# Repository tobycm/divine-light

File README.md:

# Divine Light

CH572-powered RGB flashlight with BLE for remote control from phone. Uses SK6812s for high brightness and 2 LiPos for portable usage. Provides charging port and one reverse charging port (acts as power bank).

## PCB

## BOM

| Description | Quantity | Part # | Unit price | Extended Price USD | Product Link |
| :--- | :---: | :--- | :---: | :---: | :--- |
| Lithium Battery SOT-23-6 Battery Management | 5 | HY2120-CB | 0.251 | 1.26 | https://www.lcsc.com/product-detail/C116509.html |
| Battery Charging IC Battery Balancing IC Lithium-ion/Polymer VQFN-24-EP(4x4) | 2 | IP2326 | 0.6377 | 1.28 | https://www.lcsc.com/product-detail/C2832094.html |
| N-Channel Array 20V 6A 1.5W Surface Mount SOT-23-6L | 10 | FS8205A | 0.058 | 0.58 | https://www.lcsc.com/product-detail/C908265.html |
| 125mW 330Ω 150V Thick Film Resistor ±100ppm/°C ±1% 0805 Chip Resistor - Surface Mount RoHS | 100 | RC0805FR-07330RL | 0.0061 | 0.61 | https://www.lcsc.com/product-detail/C105878.html |
| 22uF ±20% 25V Ceramic Capacitor X5R 0805 | 30 | CL21A226MAYNNNE | 0.1078 | 3.23 | https://www.lcsc.com/product-detail/C602037.html |
| 10uF ±20% 10V Ceramic Capacitor X5R 0603 | 20 | CL10A106MP8NNNC | 0.0173 | 0.35 | https://www.lcsc.com/product-detail/C85713.html |
| Step-down type 600kHz Adjustable 2.5A SOT-23-6 Voltage Regulators - DC DC Switching Regulators | 5 | TP6327GS6-A | 0.3619 | 1.81 | https://www.lcsc.com/product-detail/C2901328.html |
| SMD-4P, 5.4x5mm LED Addressable, Specialty RoHS | 50 | SK6812 | 0.0726 | 3.63 | https://www.lcsc.com/product-detail/C5378720.html |
| 125mW 2kΩ 150V Thin Film Resistor ±50ppm/°C ±0.1% 0805 Chip Resistor - Surface Mount RoHS | 10 | RT0805BRE072KL | 0.0443 | 0.44 | https://www.lcsc.com/product-detail/C706274.html |
| 9.5A 2.2uH ±20% 15mΩ 10A Molded inductor SMD, 7x6.6mm Fixed Inductors RoHS | 10 | APH0630T2R2M | 0.0817 | 0.82 | https://www.lcsc.com/product-detail/C5349701.html |
| RES 180kΩ ±1% 250mW 1206 | 50 | 1206W4F1803T5E | 0.0145 | 0.725 | https://www.lcsc.com/product-detail/C17923.html |
| 5.1kΩ ±1% 100mW 0603 Thick Film Resistor | 100 | FRC0603F5101TS | 0.0015 | 0.15 | https://www.lcsc.com/product-detail/C2907044.html |
| USB-C (USB TYPE-C) Receptacle Connector 16 Position Surface Mount, Right Angle | 20 | TYPE-C 16PIN 2MD(073) | 0.0718 | 1.44 | https://www.lcsc.com/product-detail/C2765186.html |
| 100nF ±10% 50V Ceramic Capacitor X7R 0603 | 100 | CL10B104KB8NNNC | 0.0072 | 0.72 | https://www.lcsc.com/product-detail/C1591.html |
| 56kΩ ±1% 100mW 0603 Thick Film Resistor | 100 | FRC0603F5602TS | 0.0018 | 0.18 | https://www.lcsc.com/product-detail/C2907053.html |
| 100mW 10kΩ 75V Thick Film Resistor ±100ppm/°C ±1% 0603 Chip Resistor - Surface Mount RoHS | 100 | RC0603FR-0710KL | 0.0027 | 0.27 | https://www.lcsc.com/product-detail/C98220.html |
| NTC Thermistor 100kΩ Surface Mount 0603 | 50 | CMFA104J3950HANT | 0.0165 | 0.83 | https://www.lcsc.com/product-detail/C338607.html |
| 82kΩ ±1% 100mW 0603 Thick Film Resistor | 100 | FRC0603F8202TS | 0.0016 | 0.16 | https://www.lcsc.com/product-detail/C2907072.html |
| Purple LED Indication - Discrete 0603 | 50 | XL-1608UVC-04 | 0.0122 | 0.61 | https://www.lcsc.com/product-detail/C7371898.html |
| RISC-V 32 Bit 100MHz QFN-20-EP(3x3) Microcontrollers | 10 | CH572D | 0.312 | 3.12 | https://www.lcsc.com/product-detail/C46597863.html |
| 8pF 50V Ceramic Capacitor NP0 0603 | 100 | CC0603CRNPO9BN8R0 | 0.0066 | 0.66 | https://www.lcsc.com/product-detail/C327316.html |
| Slide Switch SPDT 2A @ 125V Through Hole, Right Angle Rectangular Columnar 12.7mm | 5 | SS12D10G6-WJ | 0.2314 | 1.16 | https://www.lcsc.com/product-detail/C7431059.html |
| 100mW 0Ω 75V Thick Film Resistor ±400ppm/°C ±1% 0603 Chip Resistor - Surface Mount | 100 | FRC0603F0000TS | 0.0015 | 0.15 | https://www.lcsc.com/product-detail/C2906974.html |
| Connector Header 2 position 2mm Pitch 2A Right Angle -25°C~+85°C | 20 | S2B-PH-K-S(LF)(SN) | 0.04 | 0.80 | https://www.lcsc.com/product-detail/C173752.html |
| 74mΩ 2 SOT-583 OR Controllers, Ideal Diodes RoHS | 1 | LM66200DRLR | 0.4213 | 0.4213 | https://www.lcsc.com/product-detail/C3235556.html |
| 4.7uF ±10% 10V Ceramic Capacitor X5R 0603 | 50 | CL10A475KP8NNNC | 0.0128 | 0.64 | https://www.lcsc.com/product-detail/C1705.html |
| 4 480Mbps USB 2.0 QFN-16(3x3) Interface Controllers RoHS | 1 | CH334P | 0.4073 | 0.4073 | https://www.lcsc.com/product-detail/C5373042.html |
| 300kΩ ±1% 250mW 1206 Thick Film Resistor | 100 | FRC1206F3003TS | 0.004 | 0.40 | https://www.lcsc.com/product-detail/C2933671.html |
| LCSC Shipping | 1 | LCSC Shipping | 12.38 | 12.38 | https://www.lcsc.com/ |
| PCB | 1 | PCB | 2 | 2.00 | https://jlcpcb.com/ |
| Stencil | 1 | Stencil | 3.1 | 3.10 | https://jlcpcb.com/ |
| JLCPCB Shipping | 1 | JLCPCB Shipping | 10.12 | 10.12 | https://jlcpcb.com/ |
| 103040 LiPo batteries | 2 | 103040 | 3.97 | 7.94 | https://ydlbattery.com/en-ca/products/3-7v-1200mah-103040-lithium-polymer-ion-battery?variant=42093666959513 |
| YDL Shipping | 1 | YDL Shipping | 6.98 | 6.98 | https://ydlbattery.com/en-ca |
| | | **Total:** | | **69.37** | |

## End notes

Made with <3 by @tobycm

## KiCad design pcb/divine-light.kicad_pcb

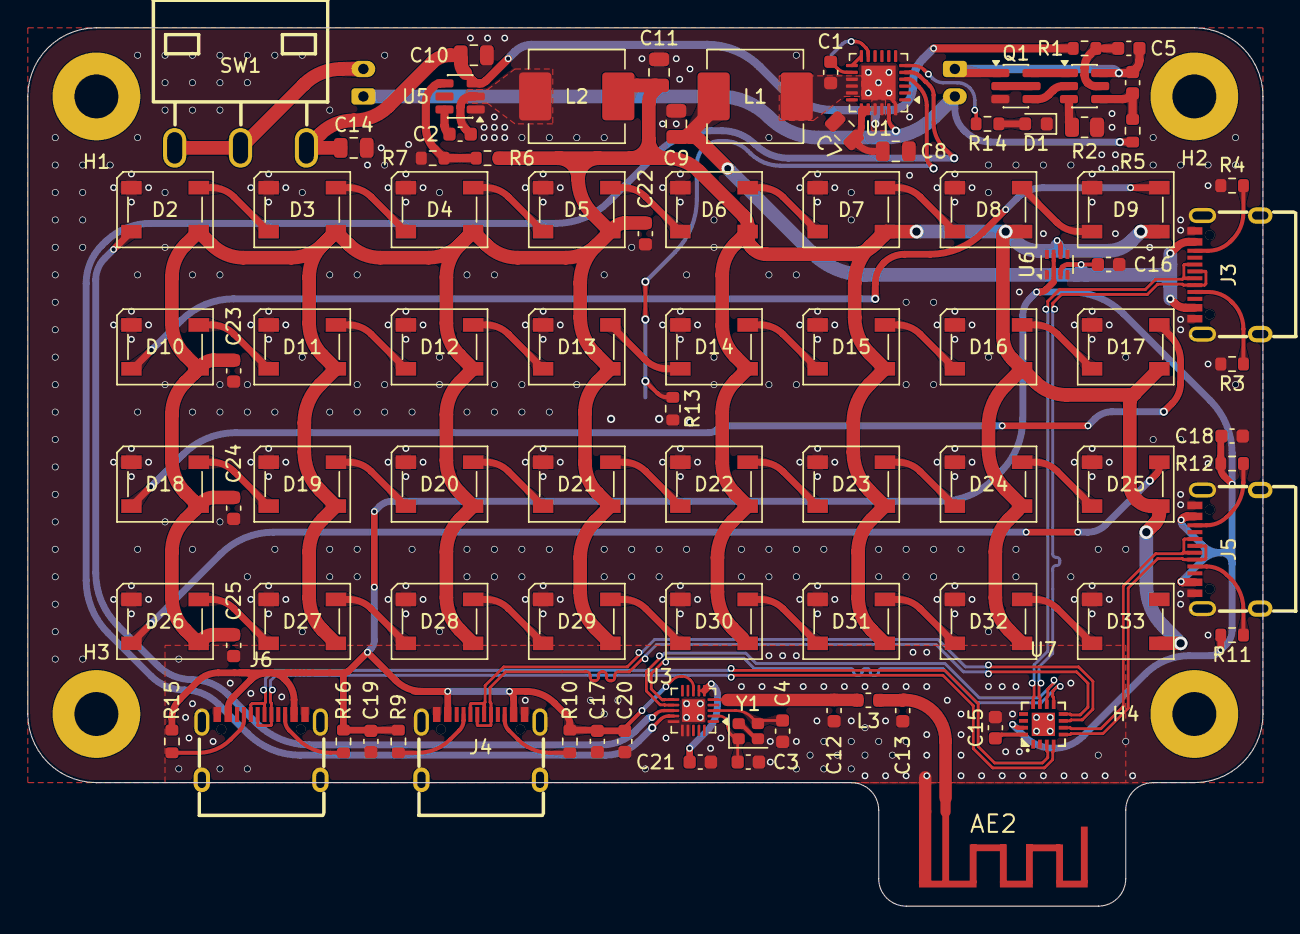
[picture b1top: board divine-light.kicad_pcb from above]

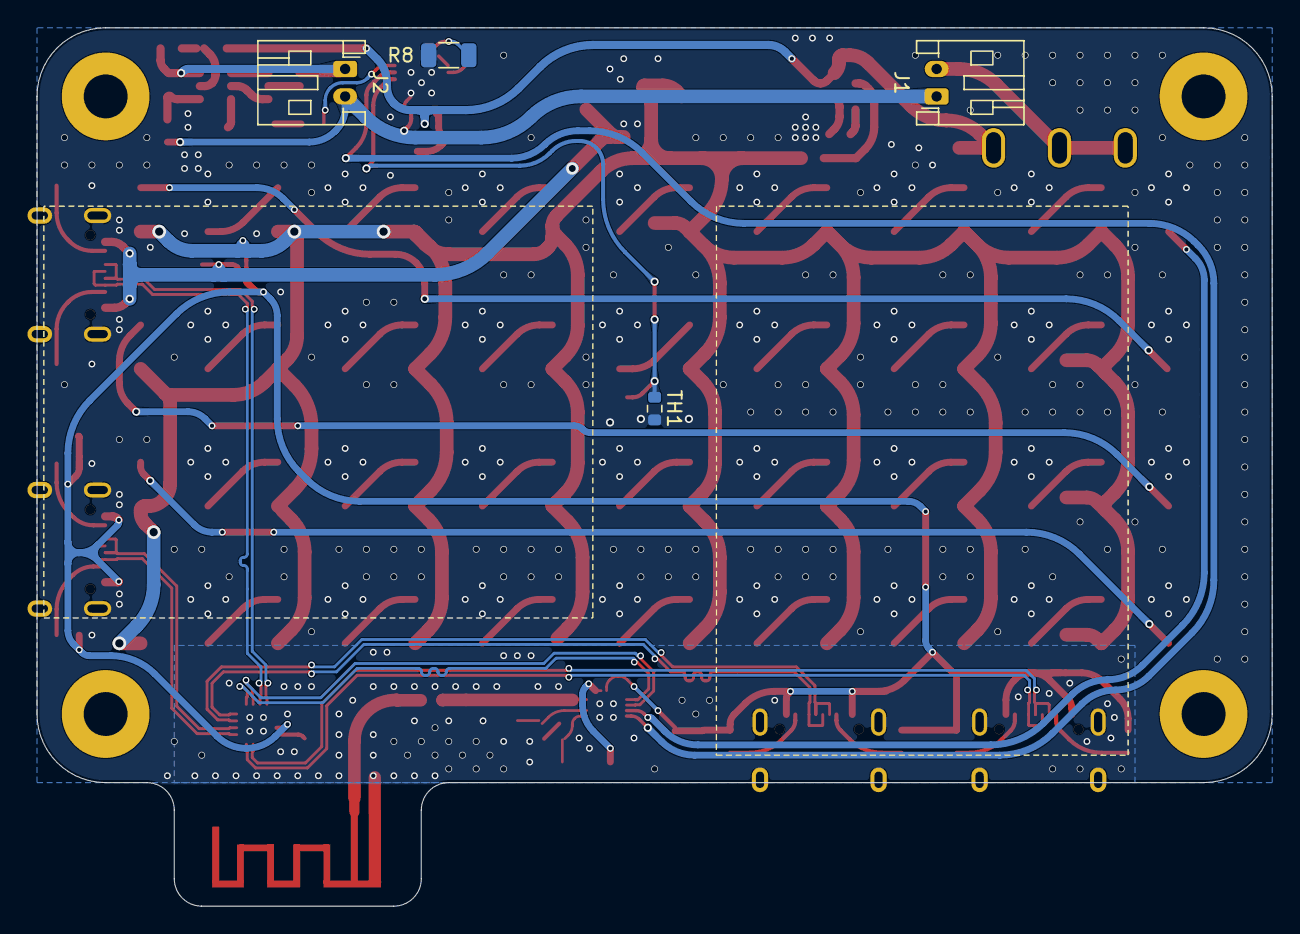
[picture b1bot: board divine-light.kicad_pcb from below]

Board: 2 copper layers, 90.0 x 64.0 mm, 98 parts (4 on the bottom side), 82 nets.

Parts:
AE2: Antenna_Shield; ANT-F-1-2.4G-1.6MM-FR4-WCH
C1, C2, C5, C6: 100n; C_0603_1608Metric
C3, C4: 8p; C_0603_1608Metric
C7, C8, C9, C10, C11, C14: 22u; C_0805_2012Metric
C12, C13: C; C_0603_1608Metric
C15, C16, C17, C18, C19, C20, C21, C22, C23, C24, C25: 4.7u; C_0603_1608Metric
D1: LED; LED_0603_1608Metric
D2, D3, D4, D5, D6, D7, D8, D9, D10, D11, D12, D13, D14, D15, D16, D17, D18, D19, D20, D21, D22, D23, D24, D25, D26, D27, D28, D29, D30, D31, D32, D33: SK6812; LED_SK6812_PLCC4_5.0x5.0mm_P3.2mm
H1, H2, H3, H4: MountingHole; MountingHole_3.2mm_M3_Pad
J1, J2: Battery_JST; JST_PH_S2B-PH-K_1x02_P2.00mm_Horizontal
J3, J4, J5, J6: USB_C_Receptacle_USB2.0_14P; USB-C-SMD_TYPE-C-16PIN-2MD-073
L1, L2: 2.2u; L_APV_APH0630
L3: L; L_0603_1608Metric
Q1: FS8205A; SOT-23-6
R1, R5, R14: 330; R_0603_1608Metric
R2: 2k; R_0805_2012Metric
R3, R4: 5.1k; R_0603_1608Metric
R6: 10k; R_0603_1608Metric
R7, R9, R10, R11, R12, R15, R16: 56k; R_0603_1608Metric
R8: 180k; R_1206_3216Metric
R13: 82k; R_0603_1608Metric
SW1: SS12D10G6-WJ; SW-TH_3P-P4.80_HX-SS12D10G6-WJ
TH1: 100k @ 3950K; R_0603_1608Metric
U1: IP2326; VQFN-24-1EP_4x4mm_P0.5mm_EP2.5x2.5mm
U2: HY2120CB; SOT-23-6
U3: CH572D; QFN-20-1EP_3x3mm_P0.4mm_EP1.65x1.65mm
U5: TPS54308; SOT-23-6
U6: LM66200DRLR; SOT-583-8
U7: CH334P; QFN-16_L3.0-W3.0-P0.50-BL-EP1.7
Y1: 32Mhz; Crystal_SMD_2016-4Pin_2.0x1.6mm

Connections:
+3V3: C21.1, U3.6 (VDD33), U3.7 (VIO33)
+3V3_USB: C15.1, U7.16 (VDD33)
+5V: C11.1, C22.1, C23.1, C24.1, C25.1, D2.3 (VDD), D3.3 (VDD), D4.3 (VDD), D5.3 (VDD), D6.3 (VDD), D7.3 (VDD), D8.3 (VDD), D9.3 (VDD), D10.3 (VDD), D11.3 (VDD), D12.3 (VDD), D13.3 (VDD), D14.3 (VDD), D15.3 (VDD), D16.3 (VDD), D17.3 (VDD), D18.3 (VDD), D19.3 (VDD), D20.3 (VDD), D21.3 (VDD), D22.3 (VDD), D23.3 (VDD), D24.3 (VDD), D25.3 (VDD), D26.3 (VDD), D27.3 (VDD), D28.3 (VDD), D29.3 (VDD), D30.3 (VDD), D31.3 (VDD), D32.3 (VDD), D33.3 (VDD), L2.2, R6.2, U6.6 (VIN2)
+5V_USB: C17.1, C18.1, C19.1, C20.1, J4.A4 (VBUS), J4.B4 (VBUS), J5.A4 (VBUS), J5.B4 (VBUS), J6.A4 (VBUS), J6.B4 (VBUS), R9.2, R10.2, R11.2, R12.2, R15.2, R16.2, U3.8 (V5), U6.2 (VOUT), U6.7 (VOUT), U7.15 (V5)
+BATT: C10.1, C14.1, R1.1, SW1.1, U1.21 (VOUT), U1.22 (VOUT), U5.3 (VIN)
-BATT: C5.2, C6.2, J2.1, Q1.1 (S1), U2.6 (VSS)
/ANT: C12.1, L3.1, U3.5 (ANT)
/Battery/STAT: U1.5 (BAT_STAT), U3.14 (PA5/SCK/SCL3)
/Battery/VC: J1.1, J2.2, R5.1, U1.23 (VBATM)
/D1D+: J4.A6 (D+), J4.B6 (D+), U7.8 (DP2)
/D1D-: J4.A7 (D-), J4.B7 (D-), U7.7 (DM2)
/D2D+: J5.A6 (D+), J5.B6 (D+), U7.6 (DP3)
/D2D-: J5.A7 (D-), J5.B7 (D-), U7.5 (DM3)
/D3D+: J6.A6 (D+), J6.B6 (D+), U7.4 (DP4)
/D3D-: J6.A7 (D-), J6.B7 (D-), U7.3 (DM4)
/MD+: U3.12 (PA1/UDP/R3/T2/SDA1), U7.10 (DP1)
/MD-: U3.11 (PA0/UDM/R2/T3/SCL1), U7.9 (DM1)
/Neopixel/DIN: D2.2 (DIN), U3.13 (PA4/SCS/PWM4/TMR2)
/UD+: J3.A6 (D+), J3.B6 (D+), U7.12 (DPU)
/UD-: J3.A7 (D-), J3.B7 (D-), U7.11 (DMU)
GND: AE2.2 (Shield), C3.2, C4.2, C7.2, C8.2, C9.2, C10.2, C11.2, C12.2, C13.2, C14.2, C15.2, C16.2, C17.2, C18.2, C19.2, C20.2, C21.2, C22.2, C23.2, C24.2, C25.2, D1.1 (K), D2.1 (VSS), D3.1 (VSS), D4.1 (VSS), D5.1 (VSS), D6.1 (VSS), D7.1 (VSS), D8.1 (VSS), D9.1 (VSS), D10.1 (VSS), D11.1 (VSS), D12.1 (VSS), D13.1 (VSS), D14.1 (VSS), D15.1 (VSS), D16.1 (VSS), D17.1 (VSS), D18.1 (VSS), D19.1 (VSS), D20.1 (VSS), D21.1 (VSS), D22.1 (VSS), D23.1 (VSS), D24.1 (VSS), D25.1 (VSS), D26.1 (VSS), D27.1 (VSS), D28.1 (VSS), D29.1 (VSS), D30.1 (VSS), D31.1 (VSS), D32.1 (VSS), D33.1 (VSS), J3.A1 (GND), J3.B1 (GND), J3.SH (SHIELD), J4.A1 (GND), J4.B1 (GND), J4.SH (SHIELD), J5.A1 (GND), J5.B1 (GND), J5.SH (SHIELD), J6.A1 (GND), J6.B1 (GND), J6.SH (SHIELD), Q1.3 (S2), R2.2, R3.2, R4.2, R7.1, R8.1, R13.2, TH1.2, U1.18 (PGND), U1.24 (VBAT_GND), U1.25 (EP), U3.15 (PA6/MISO/R4/SDA3), U3.16 (PA7/MOSI/T4/PWM1/TMR/RST_/CP1), U3.17 (PA10/R6/T7), U3.21 (GND), U5.1 (GND), U6.1 (GND), U6.4 (~ON), U6.5 (GND), U7.2 (XI), U7.17 (GND), Y1.2 (G), Y1.4 (G)
unnamed: AE2.1 (A), C13.1, L3.2
unnamed: C1.1, L1.2, U1.15 (LX), U1.16 (LX), U1.17 (LX)
unnamed: C7.1, C8.1, U1.19 (VSYS), U1.20 (VSYS)
unnamed: D1.2 (A), R14.1
unnamed: D2.4 (DOUT), D3.2 (DIN)
unnamed: D3.4 (DOUT), D4.2 (DIN)
unnamed: D4.4 (DOUT), D5.2 (DIN)
unnamed: D5.4 (DOUT), D6.2 (DIN)
unnamed: D6.4 (DOUT), D7.2 (DIN)
unnamed: D7.4 (DOUT), D8.2 (DIN)
unnamed: D8.4 (DOUT), D9.2 (DIN)
unnamed: D9.4 (DOUT), D10.2 (DIN)
unnamed: D10.4 (DOUT), D11.2 (DIN)
unnamed: D11.4 (DOUT), D12.2 (DIN)
unnamed: D12.4 (DOUT), D13.2 (DIN)
unnamed: D13.4 (DOUT), D14.2 (DIN)
unnamed: D14.4 (DOUT), D15.2 (DIN)
unnamed: D15.4 (DOUT), D16.2 (DIN)
unnamed: D16.4 (DOUT), D17.2 (DIN)
unnamed: D17.4 (DOUT), D18.2 (DIN)
unnamed: D18.4 (DOUT), D19.2 (DIN)
unnamed: D19.4 (DOUT), D20.2 (DIN)
unnamed: D20.4 (DOUT), D21.2 (DIN)
unnamed: D21.4 (DOUT), D22.2 (DIN)
unnamed: D22.4 (DOUT), D23.2 (DIN)
unnamed: D23.4 (DOUT), D24.2 (DIN)
unnamed: D24.4 (DOUT), D25.2 (DIN)
unnamed: D25.4 (DOUT), D26.2 (DIN)
unnamed: D26.4 (DOUT), D27.2 (DIN)
unnamed: D27.4 (DOUT), D28.2 (DIN)
unnamed: D28.4 (DOUT), D29.2 (DIN)
unnamed: D29.4 (DOUT), D30.2 (DIN)
unnamed: D30.4 (DOUT), D31.2 (DIN)
unnamed: D31.4 (DOUT), D32.2 (DIN)
unnamed: D32.4 (DOUT), D33.2 (DIN)
unnamed: J1.2, SW1.2, SW1.3
unnamed: J3.A5 (CC1), R3.1
unnamed: J3.B5 (CC2), R4.1
unnamed: J4.A5 (CC1), R9.1
unnamed: J4.B5 (CC2), R10.1
unnamed: J5.A5 (CC1), R11.1
unnamed: J5.B5 (CC2), R12.1
unnamed: J6.A5 (CC1), R15.1
unnamed: J6.B5 (CC2), R16.1
unnamed: Q1.2 (D1), Q1.5 (D2)
unnamed: Q1.6 (G1), U2.1 (OD)
unnamed: Q1.4 (G2), U2.2 (OC)
unnamed: C1.2, U1.14 (BST)
unnamed: U1.12 (EN), U1.13 (VIN)
unnamed: R8.2, U1.11 (ISET)
unnamed: R14.2, U1.6 (LED)
unnamed: R13.1, TH1.1, U1.4 (NTC)
unnamed: R2.1, U2.3 (CS)
unnamed: C6.1, R5.2, U2.4 (VC)
unnamed: C5.1, R1.2, U2.5 (VDD)
unnamed: C4.1, U3.3 (XI), Y1.3
unnamed: C3.1, U3.2 (XO), Y1.1
unnamed: C2.1, U5.6 (BOOT)
unnamed: R6.1, R7.2, U5.4 (FB)
unnamed: C2.2, L2.1, U5.2 (SW)
VBUS: C9.1, C16.1, J3.A4 (VBUS), J3.B4 (VBUS), L1.1, U6.3 (VIN1)

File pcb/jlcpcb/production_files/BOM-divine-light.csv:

Comment,Designator,Footprint,LCSC,Quantity
100k @ 3950K,TH1,R_0603_1608Metric,C338607,1
100n,"C1,C2,C5,C6",C_0603_1608Metric,C1591,4
10k,R6,R_0603_1608Metric,C98220,1
180k,R8,R_1206_3216Metric,C17923,1
2.2u,"L1,L2",L_APV_APH0630,C5349701,2
22u,"C10,C11,C14,C7,C8,C9",C_0805_2012Metric,C602037,6
2k,R2,R_0805_2012Metric,C706274,1
32Mhz,Y1,Crystal_SMD_2016-4Pin_2.0x1.6mm,C2965582,1
330,"R1,R14,R5",R_0603_1608Metric,C105878,3
4.7u,"C15,C16,C17,C18,C19,C20,C21,C22,C23,C24,C25",C_0603_1608Metric,C1705,11
5.1k,"R3,R4",R_0603_1608Metric,C2907044,2
56k,"R10,R11,R12,R15,R16,R7,R9",R_0603_1608Metric,C2907053,7
82k,R13,R_0603_1608Metric,C2907072,1
8p,"C3,C4",C_0603_1608Metric,C327316,2
Battery_JST,"J1,J2",JST_PH_S2B-PH-K_1x02_P2.00mm_Horizontal,C173752,2
CH334P,U7,QFN-16_L3.0-W3.0-P0.50-BL-EP1.7,C5373042,1
CH572D,U3,QFN-20-1EP_3x3mm_P0.4mm_EP1.65x1.65mm,C46597863,1
FS8205A,Q1,SOT-23-6,C2830320,1
HY2120CB,U2,SOT-23-6,C116509,1
IP2326,U1,VQFN-24-1EP_4x4mm_P0.5mm_EP2.5x2.5mm,C2832094,1
LED,D1,LED_0603_1608Metric,C7371898,1
LM66200DRLR,U6,SOT-583-8,C3235556,1
SK6812,"D10,D11,D12,D13,D14,D15,D16,D17,D18,D19,D2,D20,D21,D22,D23,D24,D25,D26,D27,D28,D29,D3,D30,D31,D32,D33,D4,D5,D6,D7,D8,D9",LED_SK6812_PLCC4_5.0x5.0mm_P3.2mm,C5378720,32
SS12D10G6-WJ,SW1,SW-TH_3P-P4.80_HX-SS12D10G6-WJ,C7431059,1
TPS54308,U5,SOT-23-6,C2901328,1
USB_C_Receptacle_USB2.0_14P,"J3,J4,J5,J6",USB-C-SMD_TYPE-C-16PIN-2MD-073,C2765186,4
L,L3,L_0603_1608Metric,,1
Antenna_Shield,AE2,ANT-F-1-2.4G-1.6MM-FR4-WCH,,1
